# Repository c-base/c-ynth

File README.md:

c-ynth
======

data collection and source files for synth

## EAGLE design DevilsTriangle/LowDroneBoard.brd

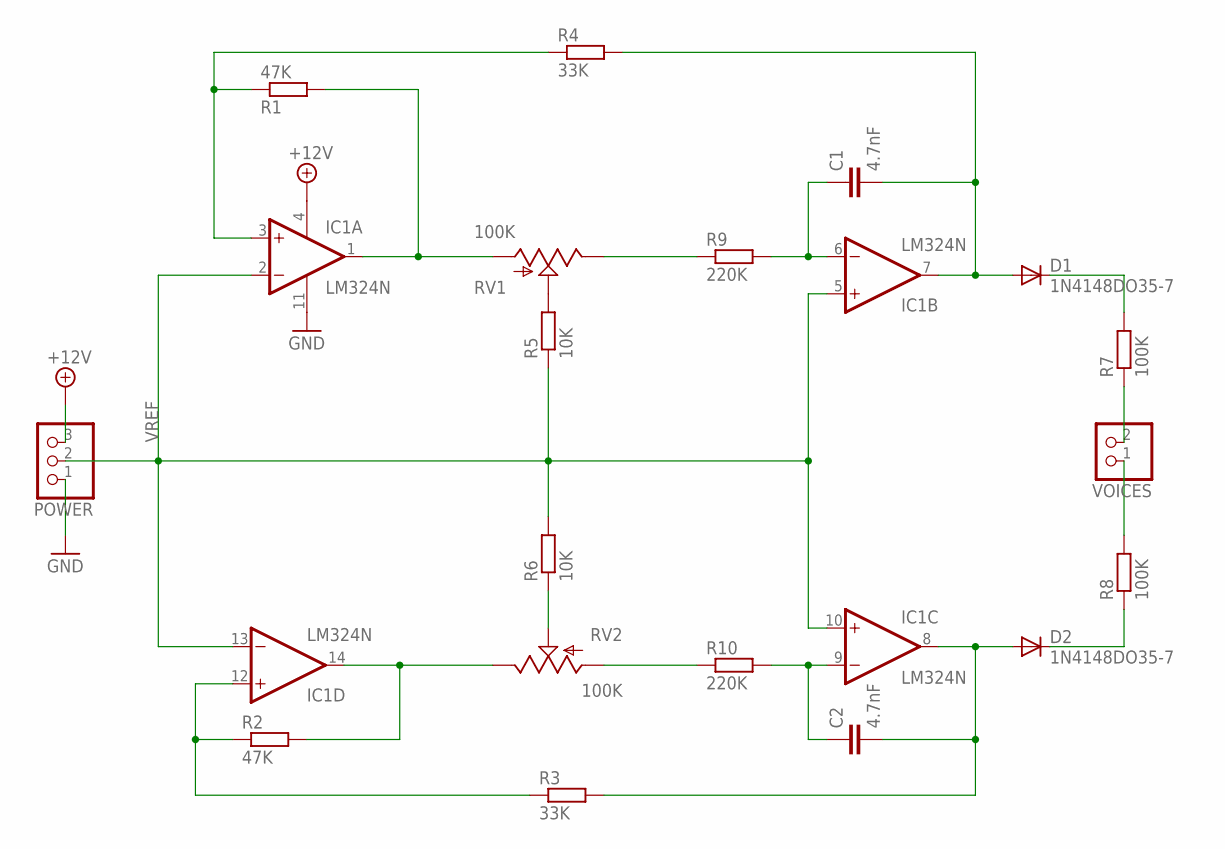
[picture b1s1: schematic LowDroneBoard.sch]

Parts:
C1, C2: 4.7nF; CAP-PTH-SMALL
D1, D2: 1N4148DO35-7; DO35-7
IC1: LM324N; DIL14
POWER: PINHD-1X3/90; 1X03/90
R1, R2: 47K; 0207/7
R3, R4: 33K; 0207/7
R5, R6: 10K; 0207/7
R7, R8: 100K; 0207/7
R9, R10: 220K; 0207/7
RV1, RV2: 100K; POT_ALPHA_RV16AF-20
VOICES: PINHD-1X2/90; 1X02/90

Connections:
+12V: IC1.4 (V+), POWER.3
GND: IC1.11 (V-), POWER.1
unnamed: IC1.12 (+IN), R2.1, R3.1
unnamed: IC1.3 (+IN), R1.1, R4.1
unnamed: IC1.1 (OUT), R1.2, RV1.1 (A)
unnamed: IC1.14 (OUT), R2.2, RV2.3 (E)
unnamed: C2.1, IC1.9 (-IN), R10.2
unnamed: R5.2, RV1.2 (S)
unnamed: R6.1, RV2.2 (S)
unnamed: R8.2, VOICES.1
unnamed: R7.1, VOICES.2
unnamed: D1.C, R7.2
unnamed: D2.C, R8.1
unnamed: C2.2, D2.A, IC1.8 (OUT), R3.2
unnamed: C1.2, D1.A, IC1.7 (OUT), R4.2
unnamed: R9.1, RV1.3 (E)
unnamed: C1.1, IC1.6 (-IN), R9.2
unnamed: R10.1, RV2.1 (A)
VREF: IC1.2 (-IN), IC1.5 (+IN), IC1.10 (+IN), IC1.13 (-IN), POWER.2, R5.1, R6.2

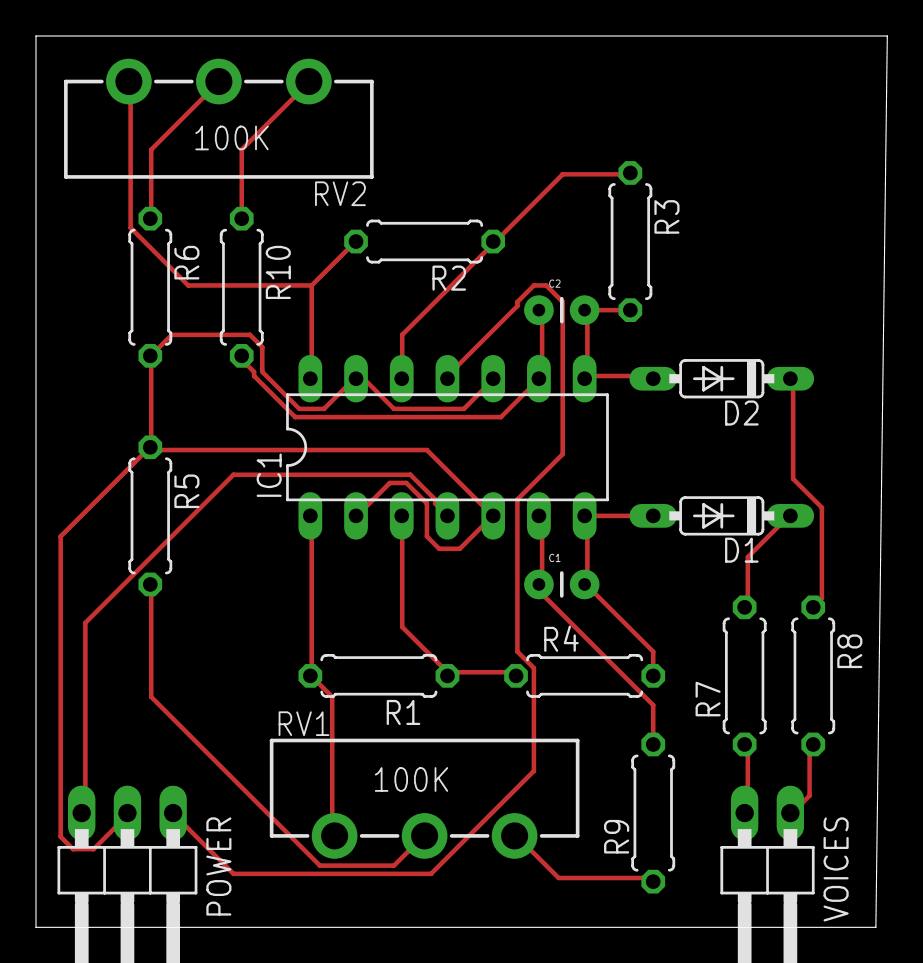
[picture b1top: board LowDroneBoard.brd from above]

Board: 2 copper layers, 47.3 x 49.5 mm, 19 parts (0 on the bottom side), 19 nets.

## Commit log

2013-12-03 added 40106 Oscillator
2013-12-10 Added Sinusgeneratoren
2013-12-10 added ICL8038
2013-12-11 added yusynth
2013-12-30 added some step sequencer links
2014-06-06 added aftertouch velocity howto
2014-06-23 added 4066 ic
2014-08-04 added pt2399 description
2015-08-20 added 4093
2015-08-25 added Circuitsnippets
2015-09-01 added Paul In The Lab
2015-09-07 added Design Your Own Distortion
2015-09-15 Devils Triangle Synth - LowDrone Schematic and Board
2016-01-28 Added OPA2134, UAF42, DRV134PA, and INA134PA
2016-01-29 added MSGEQ7
2016-03-17 added NJM2073
2016-03-21 added SchrittMacher projekt
2016-03-25 redone the devils triangle in kicad
2016-03-26 added chaosNAND project
2016-03-26 made lib path relative
2016-03-27 added c-base markings to the PCB
2016-03-28 more silkscreen
2016-04-03 added LT1054 Switched-Capacitor Voltage Converter
2018-01-14 fixed some circuit problems in schrittmacher
2018-05-26 added 4089
2018-06-01 added some links

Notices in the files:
parts and their libraries:
SparkFun-Passives: Licensing: Creative Commons ShareAlike 4.0 International - https://creativecommons.org/licenses/by-sa/4.0
